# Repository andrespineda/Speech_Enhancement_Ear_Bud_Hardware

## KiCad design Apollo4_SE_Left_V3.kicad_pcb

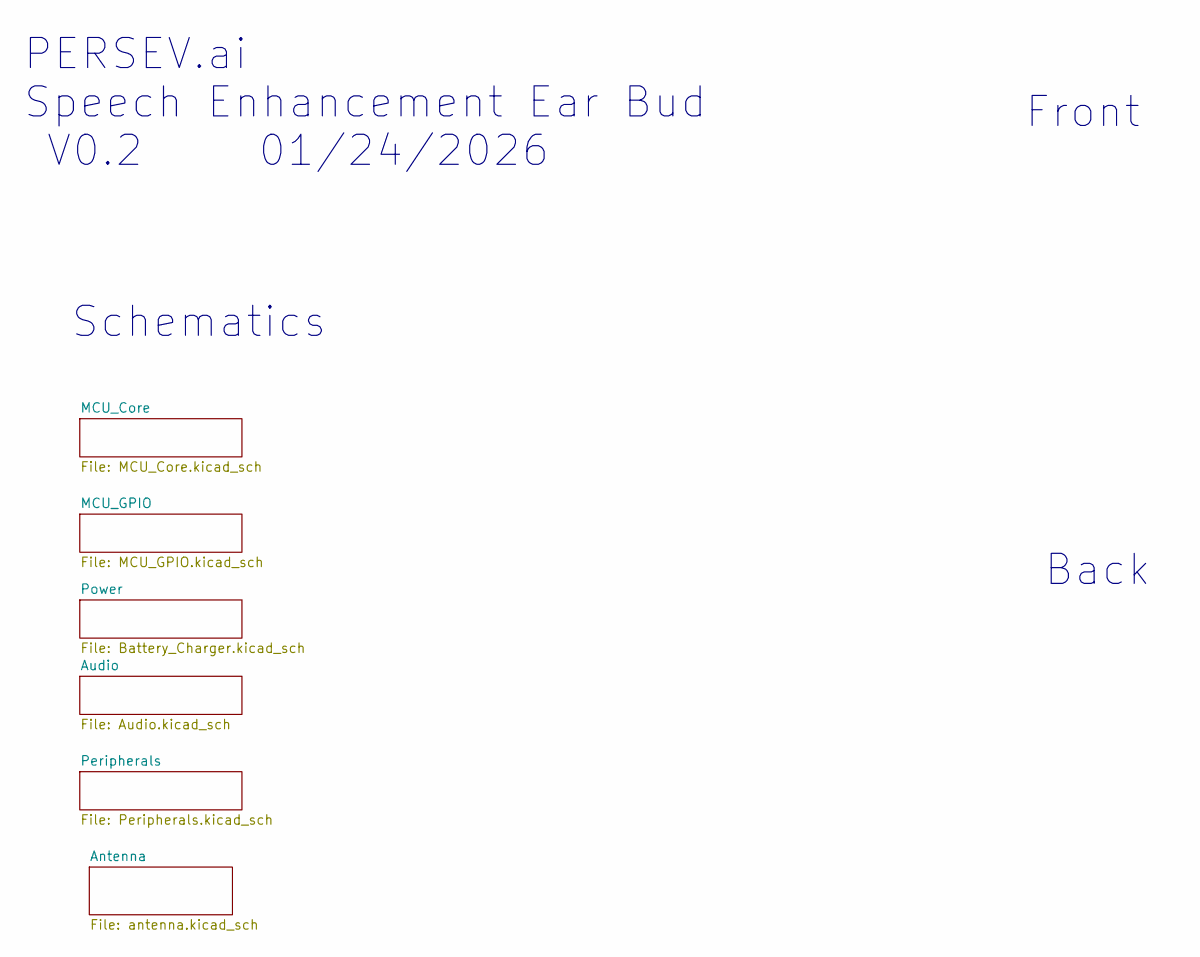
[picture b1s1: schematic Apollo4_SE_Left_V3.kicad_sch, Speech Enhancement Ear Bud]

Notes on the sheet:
Back
PERSEV.ai Speech Enhancement Ear Bud V0.2 01/24/2026
Schematics
Front

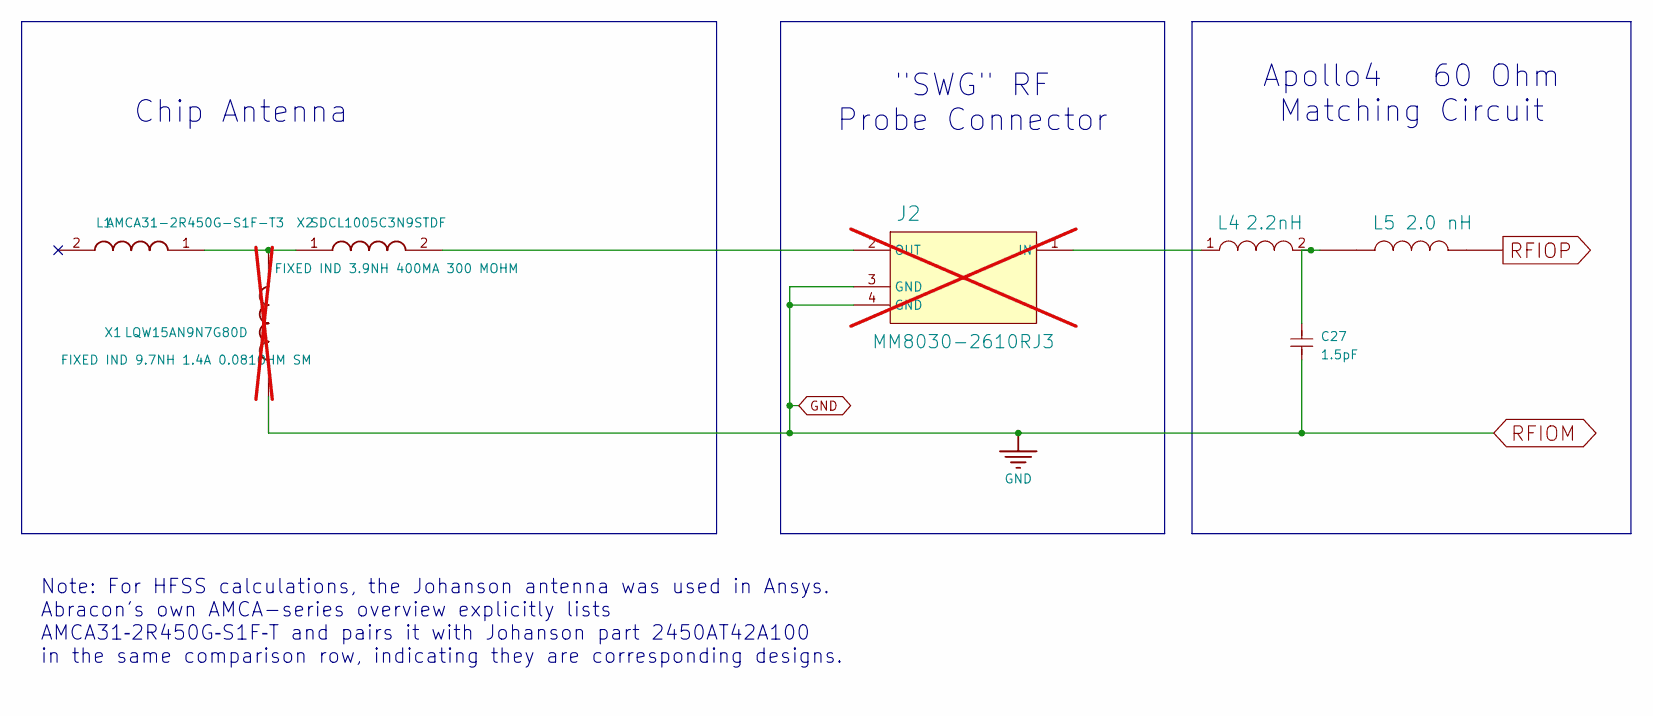
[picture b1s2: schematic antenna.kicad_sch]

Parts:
C27: 1.5pF; SMT_0201_0603Metric; Manufacturer_Part_Number GJM0335C1E1R5WB01D; LCSC Part # C435397
J2: MM8030-2610RJ3; MURATA_MM8030-2610RJ3; Digi-Key_Part_Number 490-5907-1-ND; not fitted
L1: AMCA31-2R450G-S1F-T3; ANTC3216X140N; Manufacturer_Part_Number AMCA31-2R450G-S1F-T3; LCSC C3283994
L4: 2.2nH; INDC0603X33N; Manufacturer_Part_Number LQP03TN2N2B02D; Digi-Key_Part_Number 490-6723-1-ND
L5: 2.0 nH; IND_LQP03HQ2N0B02D; Manufacturer_Part_Number LQP03HQ2N0B02D; JLCPCB Part # C98041
X1: LQW15AN9N7G80D; SMT_0402_1005Metric; Manufacturer_Part_Number LQW15AN9N7G80D; LCSC C2044467; not fitted
X2: SDCL1005C3N9STDF; SMT_0402_1005Metric; Manufacturer_Part_Number SDCL1005C3N9STDF; LCSC C14033

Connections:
GND: C27.2, J2.3 (GND), J2.4 (GND), X1.1; also elsewhere on the board
unnamed: C27.1, L4.2, L5.1
unnamed: J2.1 (IN), L4.1
unnamed: J2.2 (OUT), X2.2
unnamed: L1.1 (FEED), X1.2, X2.1
RFIOP: L5.2; also elsewhere on the board

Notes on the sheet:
Apollo4 60 Ohm Matching Circuit
Chip Antenna
Note: For HFSS calculations, the Johanson antenna was used in Ansys. Abracon's own AMCA-series overview explicitly lists AMCA31‑2R450G‑S1F‑T and pairs it with Johanson part 2450AT42A100 in the same comparison row, indicating they are corresponding designs. ​
"SWG" RF Probe Connector

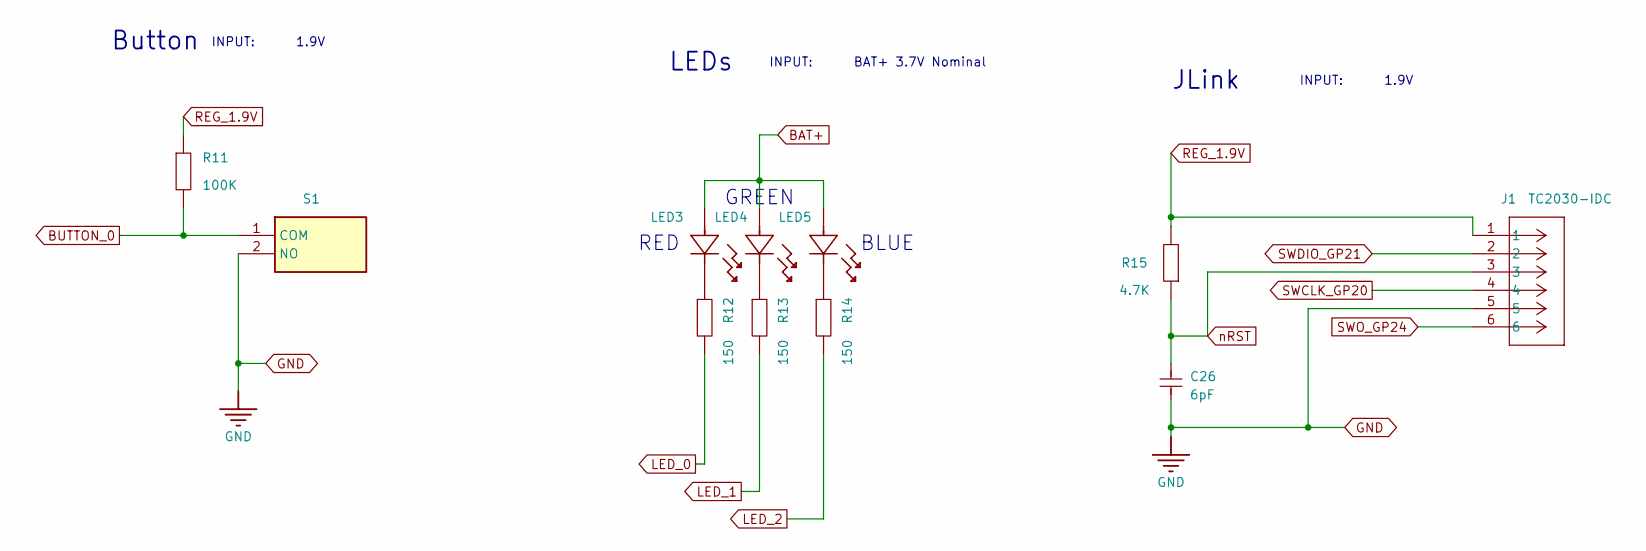
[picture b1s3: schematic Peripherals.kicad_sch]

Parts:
C26: 6pF; SMT_0201_0603Metric; Manufacturer_Part_Number GRM0335C1E6R0DA01D; LCSC C161395
J1: TC2030-IDC; TC2030_THL_PINS; Manufacturer_Part_Number DNP
LED3: XL-0201SURC; LED_0201_0603Metric; Manufacturer_Part_Number XL-0201SURC; LCSC C3646923
LED4: XL-0201UGC; LED_0201_0603Metric; Manufacturer_Part_Number XL-0201UGC; LCSC C3646922
LED5: XL-0201UBC; LED_0201_0603Metric; Manufacturer_Part_Number XL-0201UBC; LCSC C3646921
R11: 100K; SMT_0201_0603Metric; Manufacturer_Part_Number RC0201FR-07100KL; LCSC C106224
R12, R13, R14: 150; SMT_0201_0603Metric; Manufacturer_Part_Number RC0201JR-07150RL; LCSC C274881
R15: 4.7K; SMT_0201_0603Metric; Manufacturer_Part_Number RC0201FR-074K7L; LCSC C138135
S1: NANOT160AS; Manufacturer_Part_Number GSNANOT000102; LCSC C2760981

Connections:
BAT+: LED3.2, LED4.2, LED5.2; also elsewhere on the board
BUTTON_0: R11.1, S1.1 (COM); also elsewhere on the board
GND: C26.2, J1.5, S1.2 (NO); also elsewhere on the board
LED_0: R12.1; also elsewhere on the board
LED_1: R13.1; also elsewhere on the board
LED_2: R14.1; also elsewhere on the board
unnamed: LED3.1, R12.2
unnamed: LED4.1, R13.2
unnamed: LED5.1, R14.2
REG_1.9V: J1.1, R11.2, R15.1; also elsewhere on the board
SWCLK_GP20: J1.4; also elsewhere on the board
SWDIO_GP21: J1.2; also elsewhere on the board
SWO_GP24: J1.6; also elsewhere on the board
nRST: C26.1, J1.3, R15.2; also elsewhere on the board

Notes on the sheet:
INPUT: 1.9V
JLink
Button
GREEN
INPUT: 1.9V
BLUE
LEDs
RED
INPUT: BAT+ 3.7V Nominal

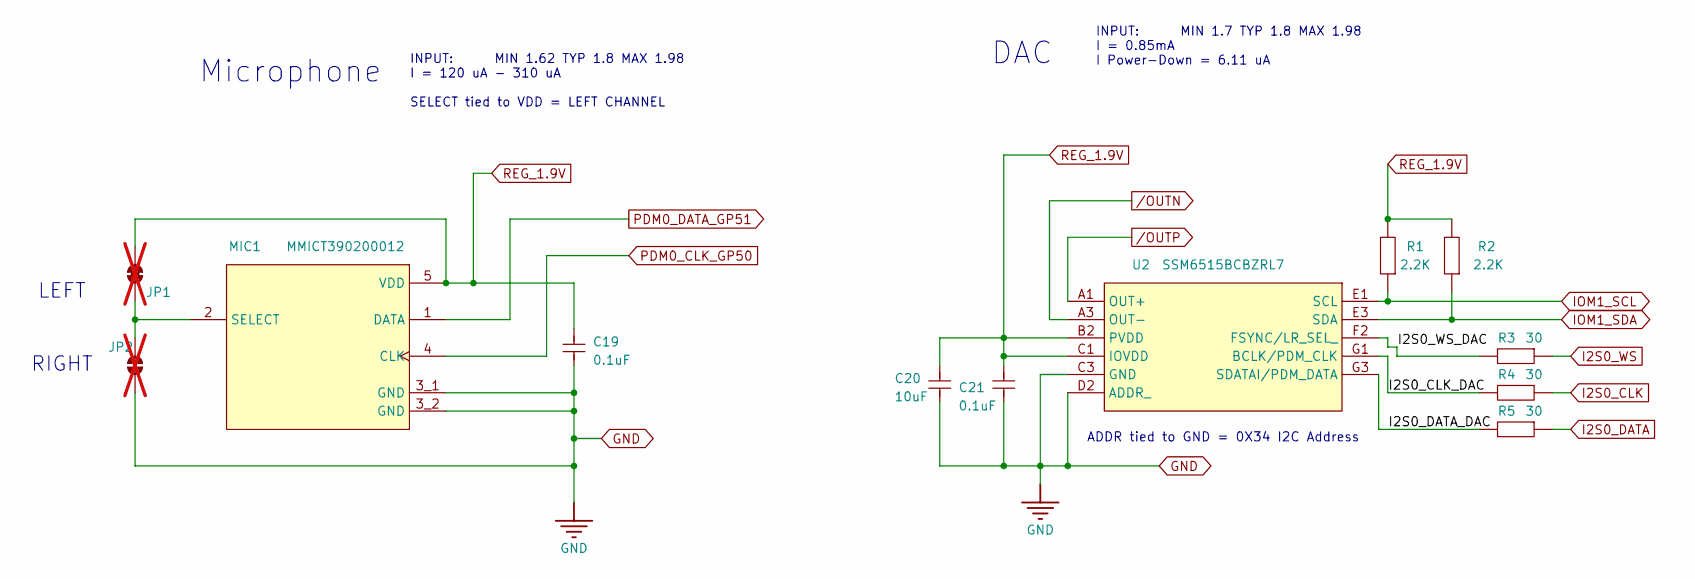
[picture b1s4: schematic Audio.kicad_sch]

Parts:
C19, C21: 0.1uF; SMT_0201_0603Metric; Manufacturer_Part_Number CC0201KRX5R7BB104; LCSC C467016
C20: 10uF; SMT_0402_1005Metric; MANUFACTURER PART NUMBER GRM155R61A106ME11D; LCSC C408132
JP1: SolderJumper_2_Bridged; SolderJumper-Tiny_CLOSED; Manufacturer_Part_Number DNP; not fitted
JP2: SolderJumper_2_Open; SolderJumper-Tiny_OPEN; Manufacturer_Part_Number DNP; not fitted
MIC1: MMICT390200012; MIC_MMICT5837-00-012; Manufacturer_Part_Number MMICT390200012; LCSC C3171752
R1, R2: 2.2K; SMT_0201_0603Metric; Manufacturer_Part_Number RC0201JR-072K2L; LCSC C138109
R3, R4, R5: 30; SMT_0201_0603Metric; Manufacturer_Part_Number RC0201FR-0730RL; LCSC C320826
U2: SSM6515BCBZRL7; SSM6515BCBZRL; Manufacturer_Part_Number SSM6515BCBZRL; Mouser Part Number *

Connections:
/Audio/I2S0_CLK_DAC: R4.1, U2.G1 (BCLK/PDM_CLK)
/Audio/I2S0_DATA_DAC: R5.1, U2.G3 (SDATAI/PDM_DATA)
/Audio/I2S0_WS_DAC: R3.1, U2.F2 (FSYNC/LR_SEL_)
GND: C19.2, C20.2, C21.2, JP2.1 (A), MIC1.3_1 (GND), MIC1.3_2 (GND), U2.C3 (GND), U2.D2 (ADDR_); also elsewhere on the board
I2S0_CLK: R4.2; also elsewhere on the board
I2S0_DATA: R5.2; also elsewhere on the board
I2S0_WS: R3.2; also elsewhere on the board
IOM1_SCL: R1.2, U2.E1 (SCL); also elsewhere on the board
IOM1_SDA: R2.2, U2.E3 (SDA); also elsewhere on the board
unnamed: JP1.2 (B), JP2.2 (B), MIC1.2 (SELECT)
PDM0_CLK_GP50: MIC1.4 (CLK); also elsewhere on the board
PDM0_DATA_GP51: MIC1.1 (DATA); also elsewhere on the board
REG_1.9V: C19.1, C20.1, C21.1, JP1.1 (A), MIC1.5 (VDD), R1.1, R2.1, U2.B2 (PVDD), U2.C1 (IOVDD); also elsewhere on the board
/OUTN: U2.A3 (OUT-)
/OUTP: U2.A1 (OUT+)

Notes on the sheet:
Microphone
RIGHT
INPUT: MIN 1.7 TYP 1.8 MAX 1.98 I = 0.85mA I Power-Down = 6.11 uA
ADDR tied to GND = 0X34 I2C Address
INPUT: MIN 1.62 TYP 1.8 MAX 1.98 I = 120 uA - 310 uA SELECT tied to VDD = LEFT CHANNEL
LEFT
DAC

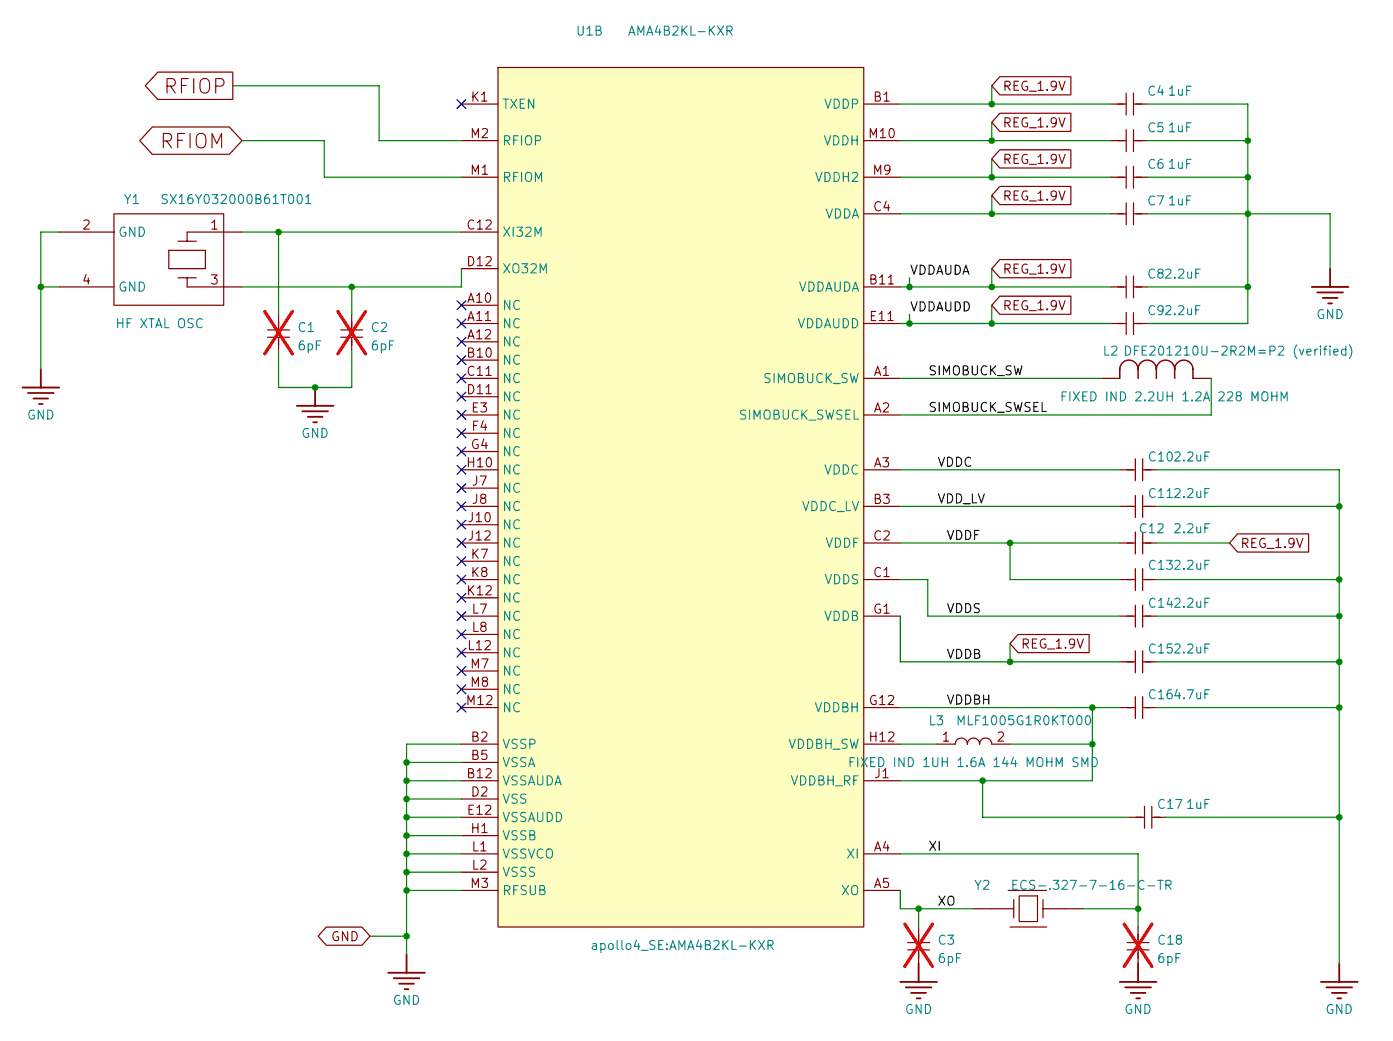
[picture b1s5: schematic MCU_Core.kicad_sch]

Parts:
C1, C2, C3, C18: 6pF; SMT_0201_0603Metric; Manufacturer_Part_Number GRM0335C1H6R0CA01D; not fitted
C4, C5, C6, C7, C17: 1uF; SMT_0201_0603Metric; Manufacturer_Part_Number GRM033R61A105ME15D; LCSC C181054
C8, C9, C10, C11, C12, C13, C14, C15: 2.2uF; SMT_0201_0603Metric; Manufacturer_Part_Number GRM033R61A225KE47D; LCSC C335106
C16: 4.7uF; SMT_0201_0603Metric; Manufacturer_Part_Number GRM035R60J475ME15D; LCSC C335103
L2: DFE201210U-2R2M=P2 (verified); IND_DFE201210U-2R2M=P2_MUR; Manufacturer_Part_Number DFE201210U-2R2M=P2; LCSC C2049745
L3: MLF1005G1R0KT000; LQW15CNR20J00B; Manufacturer_Part_Number MLF1005G1R0KT000; LCSC C516791
U1: AMA4B2KL-KXR; Manufacturer_Part_Number AMA4B2KL-KXR; LCSC C20494636
Y1: SX16Y032000B61T001; XOSC_ABM12W_1.2x1.6; Manufacturer_Part_Number SX16Y032000B61T001; LCSC C20623628
Y2: ECS-.327-7-16-C-TR; XTAL2-1P6X1P0-SM; Manufacturer_Part_Number ECS-.327-7-16-C-TR; LCSC C2449817

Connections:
/MCU_Core/SIMOBUCK_SW: L2.2, U1.A1 (SIMOBUCK_SW)
/MCU_Core/SIMOBUCK_SWSEL: L2.1, U1.A2 (SIMOBUCK_SWSEL)
/MCU_Core/VDDBH: C16.1, C17.1, L3.2, U1.G12 (VDDBH), U1.J1 (VDDBH_RF)
/MCU_Core/VDDC: C10.1, U1.A3 (VDDC)
/MCU_Core/VDDF: C12.1, C13.1, U1.C2 (VDDF)
/MCU_Core/VDDS: C14.1, U1.C1 (VDDS)
/MCU_Core/VDD_LV: C11.1, U1.B3 (VDDC_LV)
/MCU_Core/XI: C18.1, U1.A4 (XI), Y2.2
/MCU_Core/XO: C3.1, U1.A5 (XO), Y2.1
GND: C1.2, C2.2, C3.2, C4.2, C5.2, C6.2, C7.2, C8.2, C9.2, C10.2, C11.2, C13.2, C14.2, C15.2, C16.2, C17.2, C18.2, U1.B2 (VSSP), U1.B5 (VSSA), U1.B12 (VSSAUDA), U1.D2 (VSS), U1.E12 (VSSAUDD), U1.H1 (VSSB), U1.L1 (VSSVCO), U1.L2 (VSSS), U1.M1 (RFIOM), U1.M3 (RFSUB), Y1.2 (GND), Y1.4 (GND); also elsewhere on the board
unnamed: L3.1, U1.H12 (VDDBH_SW)
unnamed: C1.1, U1.C12 (XI32M), Y1.1
unnamed: C2.1, U1.D12 (XO32M), Y1.3
REG_1.9V: C4.1, C5.1, C6.1, C7.1, C8.1, C9.1, C12.2, C15.1, U1.B1 (VDDP), U1.B11 (VDDAUDA), U1.C4 (VDDA), U1.E11 (VDDAUDD), U1.G1 (VDDB), U1.M9 (VDDH2), U1.M10 (VDDH); also elsewhere on the board
RFIOP: U1.M2 (RFIOP); also elsewhere on the board

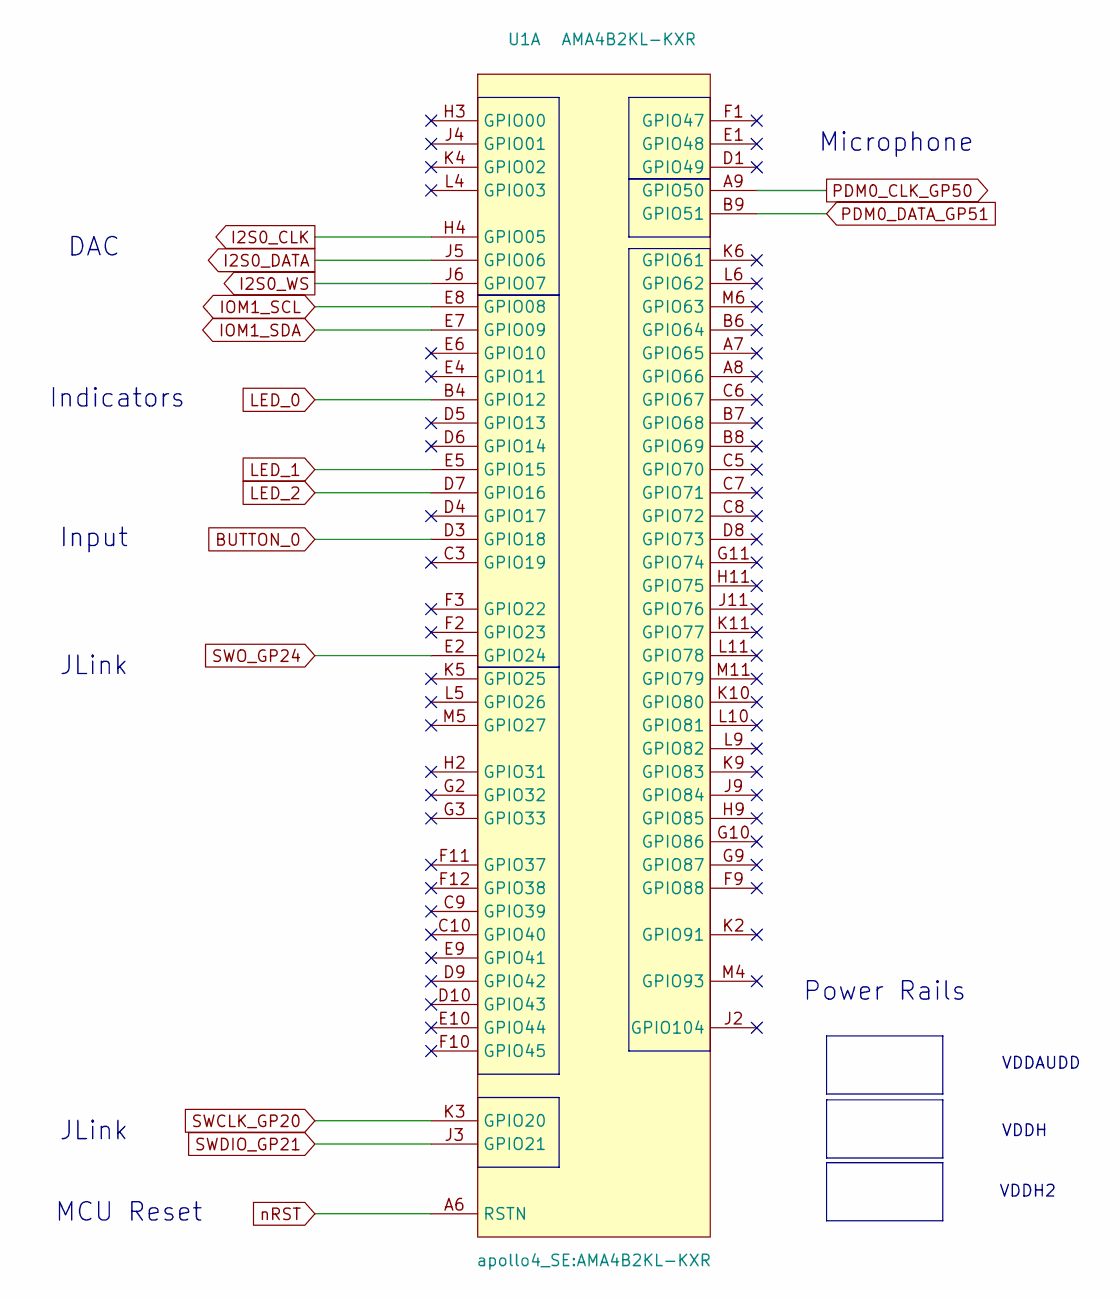
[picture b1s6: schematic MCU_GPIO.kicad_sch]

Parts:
U1: AMA4B2KL-KXR; Manufacturer_Part_Number AMA4B2KL-KXR; LCSC C20494636

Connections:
BUTTON_0: U1.D3 (GPIO18); also elsewhere on the board
I2S0_CLK: U1.H4 (GPIO05); also elsewhere on the board
I2S0_DATA: U1.J5 (GPIO06); also elsewhere on the board
I2S0_WS: U1.J6 (GPIO07); also elsewhere on the board
IOM1_SCL: U1.E8 (GPIO08); also elsewhere on the board
IOM1_SDA: U1.E7 (GPIO09); also elsewhere on the board
LED_0: U1.B4 (GPIO12); also elsewhere on the board
LED_1: U1.E5 (GPIO15); also elsewhere on the board
LED_2: U1.D7 (GPIO16); also elsewhere on the board
PDM0_CLK_GP50: U1.A9 (GPIO50); also elsewhere on the board
PDM0_DATA_GP51: U1.B9 (GPIO51); also elsewhere on the board
SWCLK_GP20: U1.K3 (GPIO20); also elsewhere on the board
SWDIO_GP21: U1.J3 (GPIO21); also elsewhere on the board
SWO_GP24: U1.E2 (GPIO24); also elsewhere on the board
nRST: U1.A6 (RSTN); also elsewhere on the board

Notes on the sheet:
Input
Power Rails
VDDH
VDDAUDD
MCU Reset
DAC
Indicators
JLink
VDDH2
Microphone

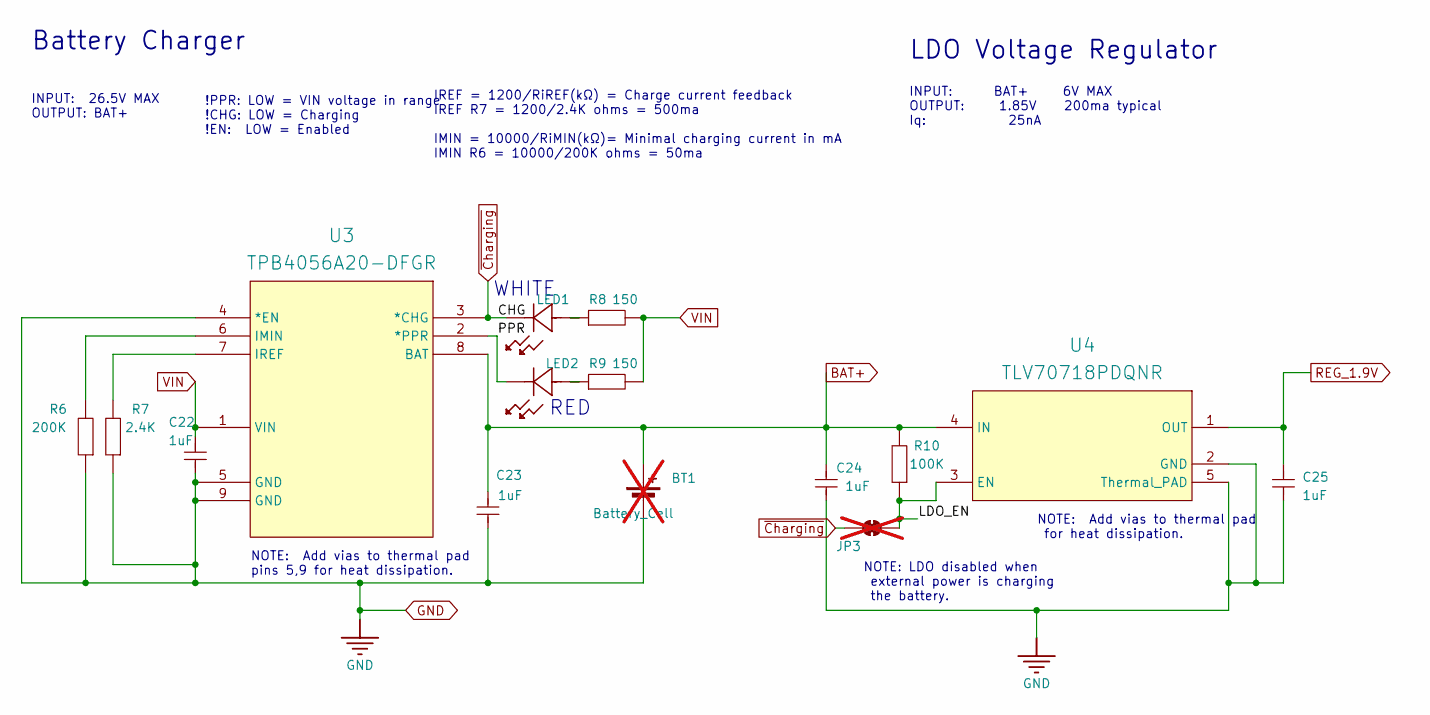
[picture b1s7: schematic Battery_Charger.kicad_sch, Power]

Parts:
BT1: Battery_Cell; not fitted
C22, C23, C24, C25: 1uF; SMT_0201_0603Metric; Manufacturer_Part_Number GRM033R61A105ME15D; LCSC C181054
JP3: SolderJumper_2_Bridged; SolderJumper-Tiny_CLOSED; Manufacturer_Part_Number DNP; not fitted
LED1: XL-0201UWC; LED_0201_0603Metric; Manufacturer_Part_Number XL-0201UWC; LCSC C965789
LED2: XL-0201SURC; LED_0201_0603Metric; Manufacturer_Part_Number XL-0201SURC; LCSC C3646923
R6: 200K; SMT_0201_0603Metric; Manufacturer_Part_Number RC0201FR-07200KL; LCSC C138163
R7: 2.4K; SMT_0201_0603Metric; Manufacturer_Part_Number RC0201FR-072K4L; LCSC C155738
R8, R9: 150; SMT_0201_0603Metric; Manufacturer_Part_Number RC0201JR-07150RL; LCSC C274881
R10: 100K; SMT_0201_0603Metric; Manufacturer_Part_Number RC0201FR-07100KL; LCSC C106224
U3: TPB4056A20-DFGR; DFN2X2-8_TPK; Manufacturer_Part_Number TPB4056A20-DFGR; LCSC C2902355
U4: TLV70718PDQNR; DQN0004A-MFG; Manufacturer_Part_Number TLV70718PDQNR; LCSC C2862295

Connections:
/Power/LDO_EN: JP3.1 (A), R10.2, U4.3 (EN)
/Power/PPR: LED2.1, U3.2 (*PPR)
BAT+: BT1.1 (+), C23.1, C24.1, R10.1, U3.8 (BAT), U4.4 (IN); also elsewhere on the board
GND: BT1.2 (-), C22.2, C23.2, C24.2, C25.2, R6.2, R7.2, U3.4 (*EN), U3.5 (GND), U3.9 (GND), U4.2 (GND), U4.5 (Thermal_PAD); also elsewhere on the board
unnamed: LED1.2, R8.2
unnamed: LED2.2, R9.2
unnamed: R6.1, U3.6 (IMIN)
unnamed: R7.1, U3.7 (IREF)
REG_1.9V: C25.1, U4.1 (OUT); also elsewhere on the board
VIN: C22.1, R8.1, R9.1, U3.1 (VIN)
~Charging: JP3.2 (B), LED1.1, U3.3 (*CHG)

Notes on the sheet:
Battery Charger
NOTE: Add vias to thermal pad pins 5,9 for heat dissipation.
INPUT: 26.5V MAX OUTPUT: BAT+
RED
!PPR: LOW = VIN voltage in range !CHG: LOW = Charging !EN: LOW = Enabled
NOTE: Add vias to thermal pad for heat dissipation.
WHITE
INPUT: BAT+ 6V MAX OUTPUT: 1.85V 200ma typical Iq: 25nA
NOTE: LDO disabled when external power is charging the battery.
IREF = 1200/RiREF(kΩ) = Charge current feedback IREF R7 = 1200/2.4K ohms = 500ma IMIN = 10000/RiMIN(kΩ)= Minimal charging current in mA IMIN R6 = 10000/200K ohms = 50ma
LDO Voltage Regulator

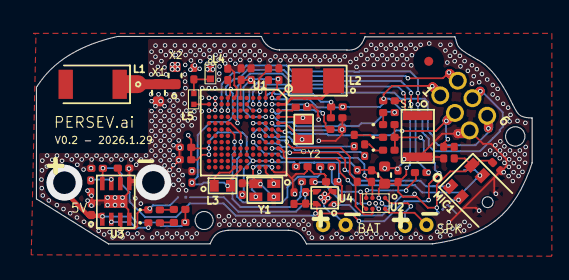
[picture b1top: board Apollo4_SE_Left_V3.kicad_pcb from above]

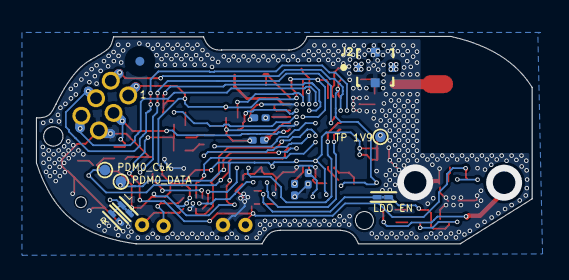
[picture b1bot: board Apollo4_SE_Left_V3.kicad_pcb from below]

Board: 2 copper layers, 27.5 x 11.5 mm, 69 parts (8 on the bottom side), 50 nets.

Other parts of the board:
BM1: Conn_01x01_MountingPin; Solderwire_8_4
BP1: Conn_01x01_MountingPin; Solderwire_8_4

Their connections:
BAT+: BP1.1; also elsewhere on the board
GND: BM1.1; also elsewhere on the board

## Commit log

2026-02-03 [PCB] See Changelog for details

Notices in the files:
parts and their libraries:
Copyright: Copyright (C) 2025 Ultra Librarian. All rights reserved.
